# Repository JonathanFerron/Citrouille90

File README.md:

# Citrouille90
DIY keyboard project - AVR-DU based - Unibody, 90 keys plus encoder and leds - Covers PCB, FW (including BL) and case.

The PCB and case work are both licensed under a Creative Commons Attribution-NonCommercial-ShareAlike 4.0 International License (CC BY-NC-SA 4.0). The Firmware is licensed under the GNU General Public License version 3: Copyright (C) 2026 Jonathan Ferron.

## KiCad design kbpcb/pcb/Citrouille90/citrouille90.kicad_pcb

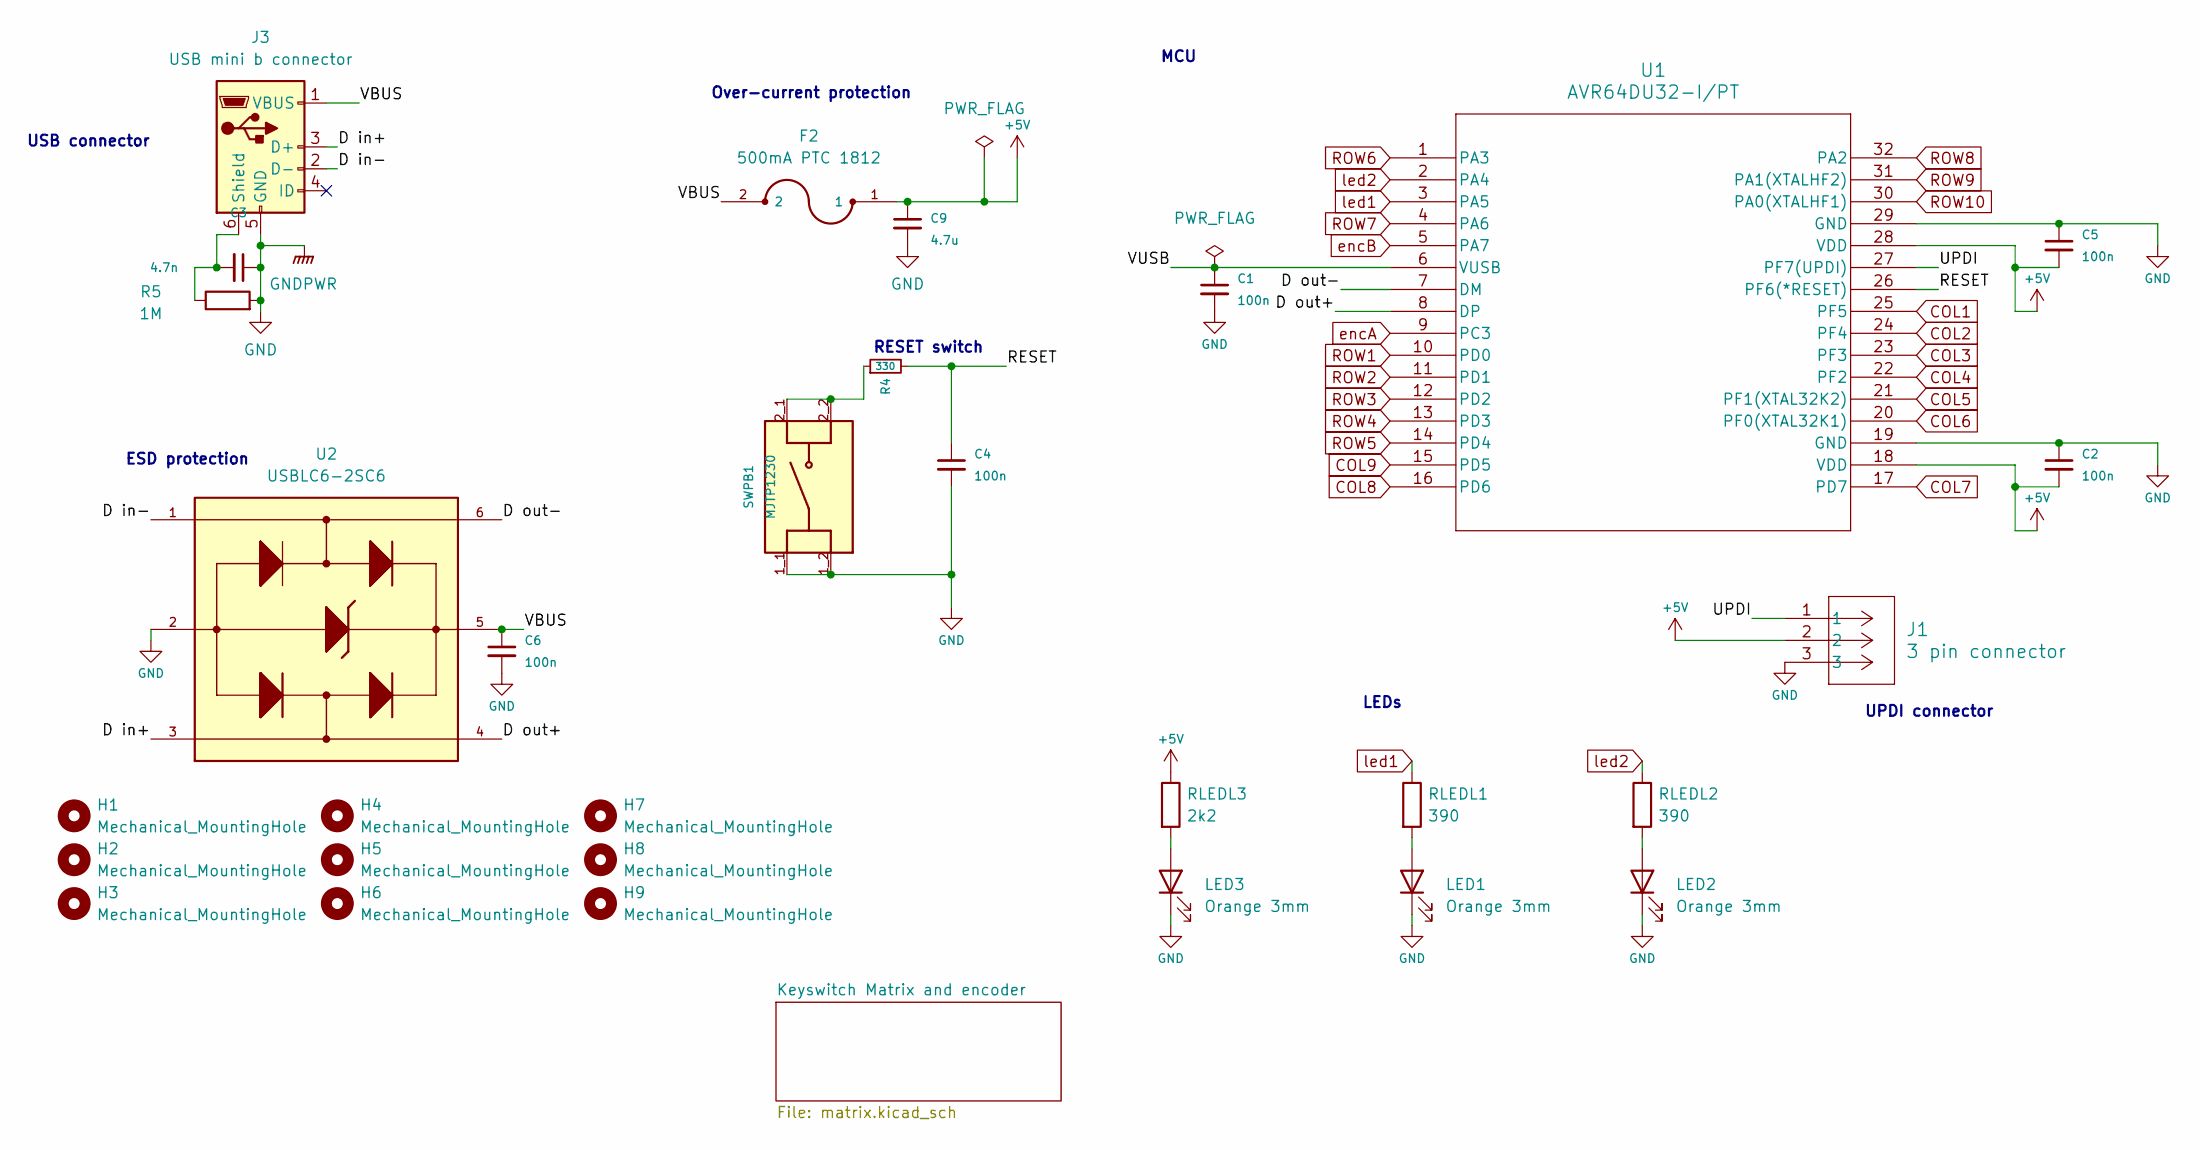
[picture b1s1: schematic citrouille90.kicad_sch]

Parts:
C1, C2, C4, C5: 100n; C_0805_2012Metric_Pad1.18x1.45mm_HandSolder; LCSC C1525
C3: 4.7n; C_0805_2012Metric_Pad1.18x1.45mm_HandSolder
C6: 100n; C_0805_2012Metric_Pad1.18x1.45mm_HandSolder
C9: 4.7u; C_1206_3216Metric_Pad1.33x1.80mm_HandSolder
F2: 500mA PTC 1812; FUSM4632X85
H1, H2, H3, H4, H5, H6, H7, H8, H9: Mechanical_MountingHole; MountingHole_2.7mm_M2.5_ISO7380_Pad
J1: 3 pin connector; PinSocket_1x03_P2.54mm_Horizontal
J3: USB mini b connector; usb mini connector
LED1, LED2, LED3: Orange 3mm; LED_D3.0mm
R4: 330; R_805
R5: 1M; R_805
RLEDL1, RLEDL2: 390; R_805
RLEDL3: 2k2; R_805
SWPB1: MJTP1230; SW_MJTP1230; PARTREV NA; LCSC C92584
U1: AVR64DU32-I/PT; TQFP32_PT_MCH-M
U2: USBLC6-2SC6; SOT-23-6

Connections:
+5V: C2.2, C5.2, C9.1, F2.1, J1.2, RLEDL3.1, U1.18 (VDD), U1.28 (VDD); also elsewhere on the board
/D out+: U1.8 (DP), U2.4; also elsewhere on the board
/D out-: U1.7 (DM), U2.6; also elsewhere on the board
/RESET: C4.1, R4.2, U1.26 (PF6(*RESET))
/UPDI: J1.1, U1.27 (PF7(UPDI))
/VBUS: C6.1, F2.2, J3.1 (VBUS), U2.5; also elsewhere on the board
/VUSB: C1.1, U1.6 (VUSB)
COL1: U1.25 (PF5); also elsewhere on the board
COL2: U1.24 (PF4); also elsewhere on the board
COL3: U1.23 (PF3); also elsewhere on the board
COL4: U1.22 (PF2); also elsewhere on the board
COL5: U1.21 (PF1(XTAL32K2)); also elsewhere on the board
COL6: U1.20 (PF0(XTAL32K1)); also elsewhere on the board
COL7: U1.17 (PD7); also elsewhere on the board
COL8: U1.16 (PD6); also elsewhere on the board
COL9: U1.15 (PD5); also elsewhere on the board
GND: C1.2, C2.1, C3.1, C4.2, C5.1, C6.2, C9.2, J1.3, J3.5 (GND), LED1.1 (K), LED2.1 (K), LED3.1 (K), R5.2, SWPB1.1_1, SWPB1.1_2, U1.19 (GND), U1.29 (GND), U2.2; also elsewhere on the board
unnamed: J3.2 (D-), U2.1
unnamed: J3.3 (D+), U2.3
unnamed 112: C3.2, J3.6 (Shield), R5.1; also elsewhere on the board
unnamed: LED1.2 (A), RLEDL1.2
unnamed: LED2.2 (A), RLEDL2.2
unnamed: LED3.2 (A), RLEDL3.2
unnamed 116: R4.1, SWPB1.2_1, SWPB1.2_2; also elsewhere on the board
ROW1: U1.10 (PD0); also elsewhere on the board
ROW2: U1.11 (PD1); also elsewhere on the board
ROW3: U1.12 (PD2); also elsewhere on the board
ROW4: U1.13 (PD3); also elsewhere on the board
ROW5: U1.14 (PD4); also elsewhere on the board
ROW6: U1.1 (PA3); also elsewhere on the board
ROW7: U1.4 (PA6); also elsewhere on the board
ROW8: U1.32 (PA2); also elsewhere on the board
ROW9: U1.31 (PA1(XTALHF2)); also elsewhere on the board
ROW10: U1.30 (PA0(XTALHF1)); also elsewhere on the board
encA: U1.9 (PC3); also elsewhere on the board
encB: U1.5 (PA7); also elsewhere on the board
led1: RLEDL1.1, U1.3 (PA5)
led2: RLEDL2.1, U1.2 (PA4)

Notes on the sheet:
Over-current protection
ESD protection
MCU
RESET switch
LEDs
UPDI connector
USB connector

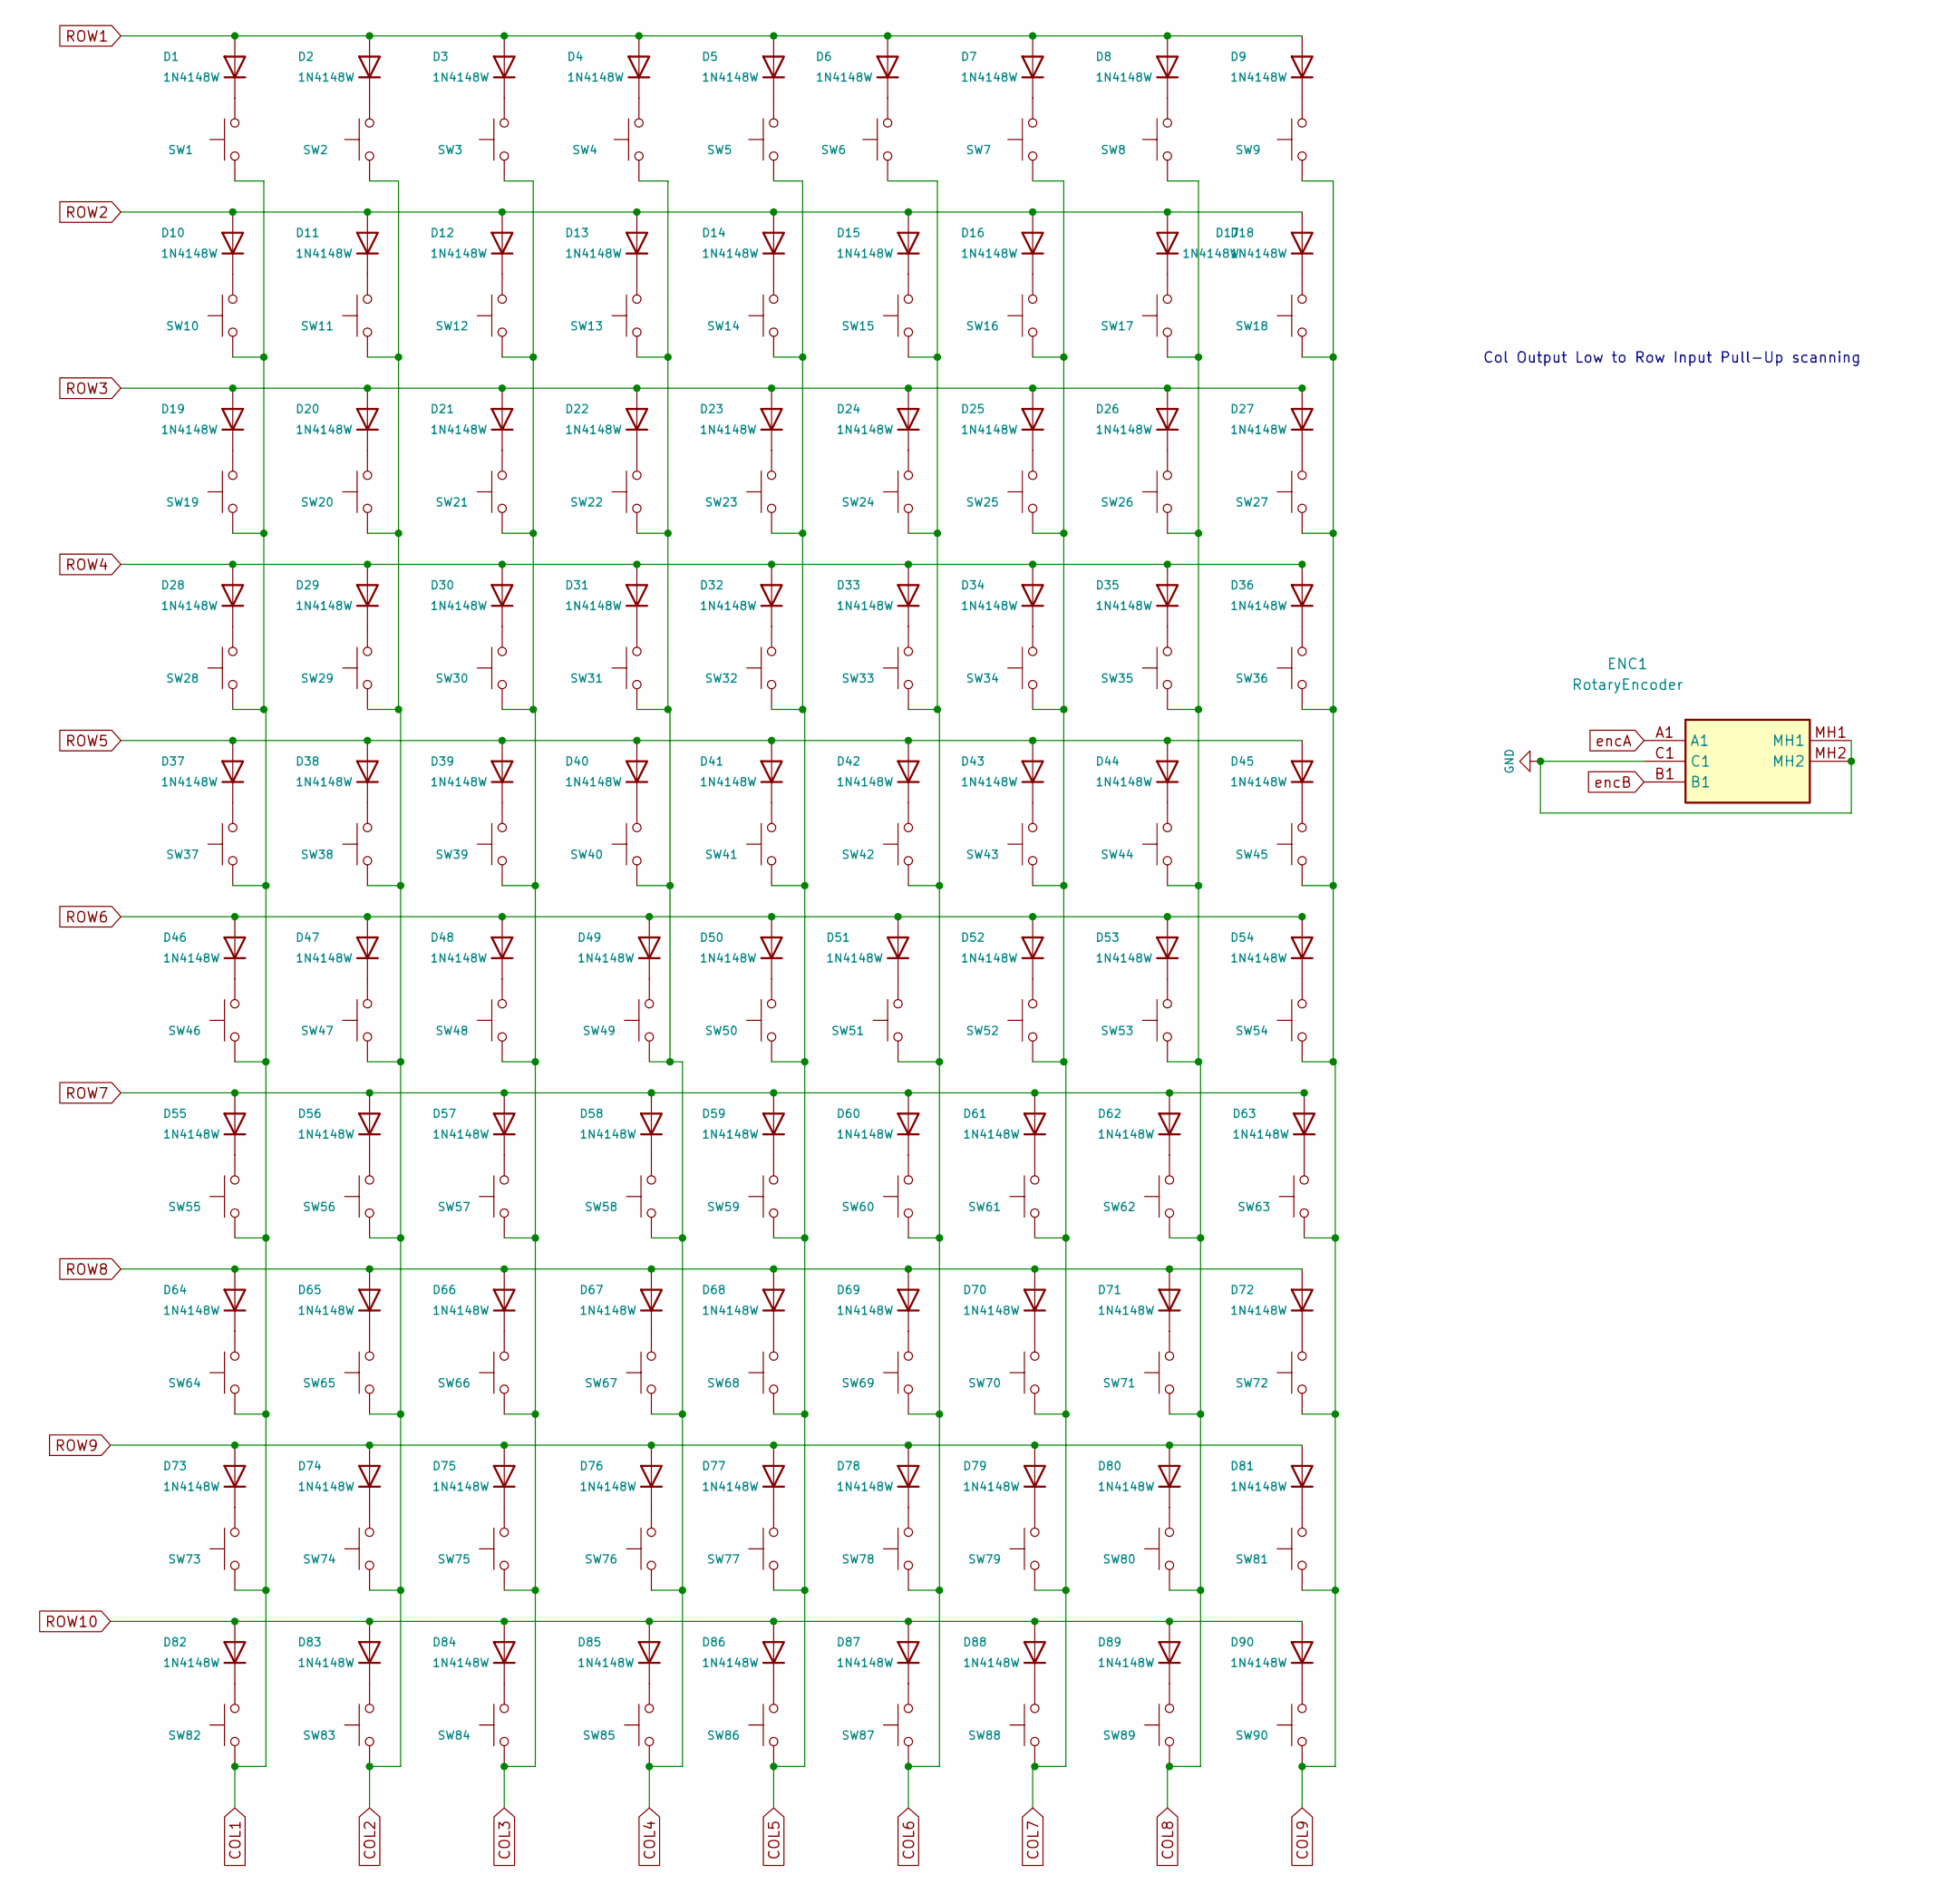
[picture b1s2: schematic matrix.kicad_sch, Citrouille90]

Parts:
D1, D2, D3, D4, D5, D6, D7, D8, D9, D10, D11, D12, D13, D14, D15, D16, D17, D18, D19, D20, D21, D22, D23, D24, D25, D26, D27, D28, D29, D30, D31, D32, D33, D34, D35, D36, D37, D38, D39, D40, D41, D42, D43, D44, D45, D46, D47, D48, D49, D50, D51, D52, D53, D54, D55, D56, D57, D58, D59, D60, D61, D62, D63, D64, D65, D66, D67, D68, D69, D70, D71, D72, D73, D74, D75, D76, D77, D78, D79, D80, D81, D82, D83, D84, D85, D86, D87, D88, D89, D90: 1N4148W; D_SOD-123; LCSC C81598
ENC1: RotaryEncoder; PES1240SN0024; Mouser Part Number 652-PES12-40S-N0024
SW1, SW2, SW3, SW4, SW5, SW6, SW7, SW8, SW9, SW10, SW11, SW12, SW13, SW14, SW15, SW16, SW17, SW18, SW19, SW20, SW21, SW22, SW23, SW24, SW25, SW26, SW27, SW28, SW29, SW30, SW31, SW32, SW33, SW34, SW35, SW36, SW37, SW38, SW39, SW40, SW41, SW42, SW43, SW44, SW45, SW46, SW47, SW48, SW49, SW50, SW51, SW52, SW53, SW54, SW55, SW56, SW57, SW58, SW59, SW60, SW61, SW62, SW63, SW64, SW65, SW66, SW67, SW68, SW69, SW70, SW71, SW72, SW73, SW74, SW75, SW76, SW77, SW78, SW79, SW80, SW81, SW82, SW83, SW84, SW85, SW86, SW87, SW88, SW89, SW90: SW_Kailh_Choc_V1_1.00u with LED indicator

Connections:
COL1: SW1.2, SW10.2, SW19.2, SW28.2, SW37.2, SW46.2, SW55.2, SW64.2, SW73.2, SW82.2; also elsewhere on the board
COL2: SW2.2, SW11.2, SW20.2, SW29.2, SW38.2, SW47.2, SW56.2, SW65.2, SW74.2, SW83.2; also elsewhere on the board
COL3: SW3.2, SW12.2, SW21.2, SW30.2, SW39.2, SW48.2, SW57.2, SW66.2, SW75.2, SW84.2; also elsewhere on the board
COL4: SW4.2, SW13.2, SW22.2, SW31.2, SW40.2, SW49.2, SW58.2, SW67.2, SW76.2, SW85.2; also elsewhere on the board
COL5: SW5.2, SW14.2, SW23.2, SW32.2, SW41.2, SW50.2, SW59.2, SW68.2, SW77.2, SW86.2; also elsewhere on the board
COL6: SW6.2, SW15.2, SW24.2, SW33.2, SW42.2, SW51.2, SW60.2, SW69.2, SW78.2, SW87.2; also elsewhere on the board
COL7: SW7.2, SW16.2, SW25.2, SW34.2, SW43.2, SW52.2, SW61.2, SW70.2, SW79.2, SW88.2; also elsewhere on the board
COL8: SW8.2, SW17.2, SW26.2, SW35.2, SW44.2, SW53.2, SW62.2, SW71.2, SW80.2, SW89.2; also elsewhere on the board
COL9: SW9.2, SW18.2, SW27.2, SW36.2, SW45.2, SW54.2, SW63.2, SW72.2, SW81.2, SW90.2; also elsewhere on the board
unnamed: D1.1 (K), SW1.1
unnamed: D2.1 (K), SW2.1
unnamed: D3.1 (K), SW3.1
unnamed: D4.1 (K), SW4.1
unnamed: D5.1 (K), SW5.1
unnamed: D6.1 (K), SW6.1
unnamed: D7.1 (K), SW7.1
unnamed: D8.1 (K), SW8.1
unnamed: D9.1 (K), SW9.1
unnamed: D10.1 (K), SW10.1
unnamed: D11.1 (K), SW11.1
unnamed: D12.1 (K), SW12.1
unnamed: D13.1 (K), SW13.1
unnamed: D14.1 (K), SW14.1
unnamed: D15.1 (K), SW15.1
unnamed: D16.1 (K), SW16.1
unnamed: D17.1 (K), SW17.1
unnamed: D18.1 (K), SW18.1
unnamed: D19.1 (K), SW19.1
unnamed: D20.1 (K), SW20.1
unnamed: D21.1 (K), SW21.1
unnamed: D22.1 (K), SW22.1
unnamed: D23.1 (K), SW23.1
unnamed: D24.1 (K), SW24.1
unnamed: D25.1 (K), SW25.1
unnamed: D26.1 (K), SW26.1
unnamed: D27.1 (K), SW27.1
unnamed: D28.1 (K), SW28.1
unnamed: D29.1 (K), SW29.1
unnamed: D30.1 (K), SW30.1
unnamed: D31.1 (K), SW31.1
unnamed: D32.1 (K), SW32.1
unnamed: D33.1 (K), SW33.1
unnamed: D34.1 (K), SW34.1
unnamed: D35.1 (K), SW35.1
unnamed: D36.1 (K), SW36.1
unnamed: D37.1 (K), SW37.1
unnamed: D38.1 (K), SW38.1
unnamed: D39.1 (K), SW39.1
unnamed: D40.1 (K), SW40.1
unnamed: D41.1 (K), SW41.1
unnamed: D42.1 (K), SW42.1
unnamed: D43.1 (K), SW43.1
unnamed: D44.1 (K), SW44.1
unnamed: D45.1 (K), SW45.1
unnamed: D46.1 (K), SW46.1
unnamed: D47.1 (K), SW47.1
unnamed: D48.1 (K), SW48.1
unnamed: D49.1 (K), SW49.1
unnamed: D50.1 (K), SW50.1
unnamed: D51.1 (K), SW51.1
unnamed: D52.1 (K), SW52.1
unnamed: D53.1 (K), SW53.1
unnamed: D54.1 (K), SW54.1
unnamed: D55.1 (K), SW55.1
unnamed: D56.1 (K), SW56.1
unnamed: D57.1 (K), SW57.1
unnamed: D58.1 (K), SW58.1
unnamed: D59.1 (K), SW59.1
unnamed: D60.1 (K), SW60.1
unnamed: D61.1 (K), SW61.1
unnamed: D62.1 (K), SW62.1
unnamed: D63.1 (K), SW63.1
unnamed: D64.1 (K), SW64.1
unnamed: D65.1 (K), SW65.1
unnamed: D66.1 (K), SW66.1
unnamed: D67.1 (K), SW67.1
unnamed: D68.1 (K), SW68.1
unnamed: D69.1 (K), SW69.1
unnamed: D70.1 (K), SW70.1
unnamed: D71.1 (K), SW71.1
unnamed: D72.1 (K), SW72.1
unnamed: D73.1 (K), SW73.1
unnamed: D74.1 (K), SW74.1
unnamed: D75.1 (K), SW75.1
unnamed: D76.1 (K), SW76.1
unnamed: D77.1 (K), SW77.1
unnamed: D78.1 (K), SW78.1
unnamed: D79.1 (K), SW79.1
unnamed: D80.1 (K), SW80.1
unnamed: D81.1 (K), SW81.1
unnamed: D82.1 (K), SW82.1
unnamed: D83.1 (K), SW83.1
unnamed: D84.1 (K), SW84.1
unnamed: D85.1 (K), SW85.1
unnamed: D86.1 (K), SW86.1
unnamed: D87.1 (K), SW87.1
unnamed: D88.1 (K), SW88.1
unnamed: D89.1 (K), SW89.1
unnamed: D90.1 (K), SW90.1
unnamed: ENC1.C1, ENC1.MH1, ENC1.MH2
ROW1: D1.2 (A), D2.2 (A), D3.2 (A), D4.2 (A), D5.2 (A), D6.2 (A), D7.2 (A), D8.2 (A), D9.2 (A); also elsewhere on the board
ROW2: D10.2 (A), D11.2 (A), D12.2 (A), D13.2 (A), D14.2 (A), D15.2 (A), D16.2 (A), D17.2 (A), D18.2 (A); also elsewhere on the board
ROW3: D19.2 (A), D20.2 (A), D21.2 (A), D22.2 (A), D23.2 (A), D24.2 (A), D25.2 (A), D26.2 (A), D27.2 (A); also elsewhere on the board
ROW4: D28.2 (A), D29.2 (A), D30.2 (A), D31.2 (A), D32.2 (A), D33.2 (A), D34.2 (A), D35.2 (A), D36.2 (A); also elsewhere on the board
ROW5: D37.2 (A), D38.2 (A), D39.2 (A), D40.2 (A), D41.2 (A), D42.2 (A), D43.2 (A), D44.2 (A), D45.2 (A); also elsewhere on the board
ROW6: D46.2 (A), D47.2 (A), D48.2 (A), D49.2 (A), D50.2 (A), D51.2 (A), D52.2 (A), D53.2 (A), D54.2 (A); also elsewhere on the board
ROW7: D55.2 (A), D56.2 (A), D57.2 (A), D58.2 (A), D59.2 (A), D60.2 (A), D61.2 (A), D62.2 (A), D63.2 (A); also elsewhere on the board
ROW8: D64.2 (A), D65.2 (A), D66.2 (A), D67.2 (A), D68.2 (A), D69.2 (A), D70.2 (A), D71.2 (A), D72.2 (A); also elsewhere on the board
ROW9: D73.2 (A), D74.2 (A), D75.2 (A), D76.2 (A), D77.2 (A), D78.2 (A), D79.2 (A), D80.2 (A), D81.2 (A); also elsewhere on the board
ROW10: D82.2 (A), D83.2 (A), D84.2 (A), D85.2 (A), D86.2 (A), D87.2 (A), D88.2 (A), D89.2 (A), D90.2 (A); also elsewhere on the board

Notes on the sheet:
Col Output Low to Row Input Pull-Up scanning

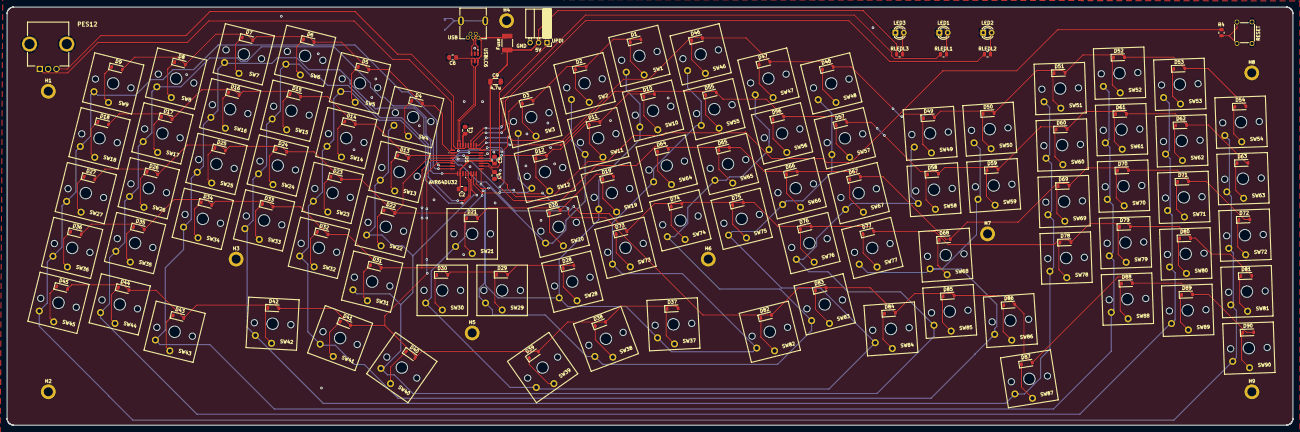
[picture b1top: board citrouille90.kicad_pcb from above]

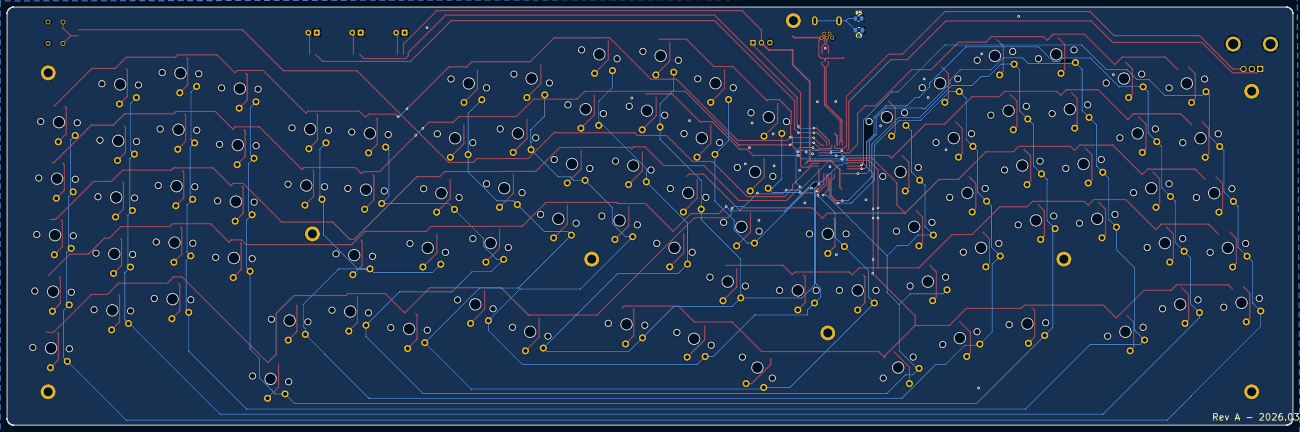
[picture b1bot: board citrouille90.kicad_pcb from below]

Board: 2 copper layers, 386.7 x 125.7 mm, 211 parts (2 on the bottom side), 128 nets.

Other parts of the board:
Fuse: 500mA PTC 1812; FUSM4632X85
PES12: RotaryEncoder; PES1240SN0024
RESET: MJTP1230; SW_MJTP1230
USB: USB mini b connector; usb mini connector
USBLC6: USBLC6-2SC6; SOT-23-6

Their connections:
+5V: Fuse.1; also elsewhere on the board
/D in+: USB.3 (D+), USBLC6.3
/D in-: USB.2 (D-), USBLC6.1
/D out+: USBLC6.4; also elsewhere on the board
/D out-: USBLC6.6; also elsewhere on the board
/VBUS: Fuse.2, USB.1 (VBUS), USBLC6.5; also elsewhere on the board
GND: PES12.C1, PES12.MH1, PES12.MH2, RESET.1_1, RESET.1_2, USB.5 (GND), USBLC6.2; also elsewhere on the board
unnamed 112: USB.6; also elsewhere on the board
unnamed 116: RESET.2_1, RESET.2_2; also elsewhere on the board
encA: PES12.A1; also elsewhere on the board
encB: PES12.B1; also elsewhere on the board

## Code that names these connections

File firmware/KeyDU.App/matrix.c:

/* matrix.c — Key matrix scan for Citrouille90 / AVR64DU32
 * Column-output-low / row-input-pullup scheme.
 * SPDX-License-Identifier: GPL-3.0-or-later
 *
 * Pin assignment (32-pin package):
 *
 *   Columns (output)
 *     PF0–PF5  →  cols 1–6   (COL_F_MASK 0x3F)
 *     PD5–PD7  →  cols 7–9   (COL_D_MASK 0xE0)
 *
 *   Rows (input, pull-up, active-low)
 *     PD0–PD4  →  rows 1–5   (ROW_D_MASK 0x1F)
 *     PA3      →  row  6
 *     PA6      →  row  7
 *     PA2      →  row  8
 *     PA1      →  row  9
 *     PA0      →  row 10     (ROW_A_MASK 0x4F)
 *
 * Note: PORTD is mixed — PD0–PD4 are row inputs, PD5–PD7 are col outputs.
 */

#include <avr/io.h>
#include <stdint.h>
#include "gpio.h"
#include "matrix.h"

/* ---------------------------------------------------------
 * Port-wide masks
 * --------------------------------------------------------- */
#define COL_F_MASK  0x3F    /* PF0–PF5  cols 1–6  */
#define COL_D_MASK  0xE0    /* PD5–PD7  cols 7–9  */
#define ROW_D_MASK  0x1F    /* PD0–PD4  rows 1–5  */
#define ROW_A_MASK  0x4F    /* PA0–PA3, PA6 rows 6–10 */

/* ---------------------------------------------------------
 * Column pin descriptors
 * --------------------------------------------------------- */
static const gpio_pin_t COL_1  = GPIO_PIN(PORTF, 0);
static const gpio_pin_t COL_2  = GPIO_PIN(PORTF, 1);
static const gpio_pin_t COL_3  = GPIO_PIN(PORTF, 2);
static const gpio_pin_t COL_4  = GPIO_PIN(PORTF, 3);
static const gpio_pin_t COL_5  = GPIO_PIN(PORTF, 4);
static const gpio_pin_t COL_6  = GPIO_PIN(PORTF, 5);
static const gpio_pin_t COL_7  = GPIO_PIN(PORTD, 5);
static const gpio_pin_t COL_8  = GPIO_PIN(PORTD, 6);
static const gpio_pin_t COL_9  = GPIO_PIN(PORTD, 7);

/* ---------------------------------------------------------
 * Row pin descriptors (init only — pull-up config)
 * --------------------------------------------------------- */
static const gpio_pin_t ROW_1  = GPIO_PIN(PORTD, 0);
static const gpio_pin_t ROW_2  = GPIO_PIN(PORTD, 1);
static const gpio_pin_t ROW_3  = GPIO_PIN(PORTD, 2);
static const gpio_pin_t ROW_4  = GPIO_PIN(PORTD, 3);
static const gpio_pin_t ROW_5  = GPIO_PIN(PORTD, 4);
static const gpio_pin_t ROW_6  = GPIO_PIN(PORTA, 3);
static const gpio_pin_t ROW_7  = GPIO_PIN(PORTA, 6);
static const gpio_pin_t ROW_8  = GPIO_PIN(PORTA, 2);
static const gpio_pin_t ROW_9  = GPIO_PIN(PORTA, 1);
static const gpio_pin_t ROW_10 = GPIO_PIN(PORTA, 0);

/* ---------------------------------------------------------
 * PORTA row bit -> logical row index (0-based)
 * __builtin_ctz(bit) gives the pin number as the LUT index.
 *   PA0 → row 9   PA1 → row 8   PA2 → row 7
 *   PA3 → row 5   PA6 → row 6
 * 0xFF marks unused/invalid entries.
 * --------------------------------------------------------- */
static const uint8_t row_a_lut[8] = {
    9, 8, 7, 5, 0xFF, 0xFF, 6, 0xFF
};

/* ---------------------------------------------------------
 * matrix_init
 * --------------------------------------------------------- */
void matrix_init(void) {
    /* Columns: latch high before enabling output to avoid glitch */
    PORTF.OUTSET = COL_F_MASK;
    PORTF.DIRSET = COL_F_MASK;
    PORTD.OUTSET = COL_D_MASK;
    PORTD.DIRSET = COL_D_MASK;

    /* Rows: inputs at reset by default — enable pull-ups only */
    GPIO_PULLUP_ENABLE(ROW_1);
    GPIO_PULLUP_ENABLE(ROW_2);
    GPIO_PULLUP_ENABLE(ROW_3);
    GPIO_PULLUP_ENABLE(ROW_4);
    GPIO_PULLUP_ENABLE(ROW_5);
    GPIO_PULLUP_ENABLE(ROW_6);
    GPIO_PULLUP_ENABLE(ROW_7);
    GPIO_PULLUP_ENABLE(ROW_8);
    GPIO_PULLUP_ENABLE(ROW_9);
    GPIO_PULLUP_ENABLE(ROW_10);
}

/* ---------------------------------------------------------
 * scan_col — drive one column low, read both row ports,
 *            dispatch any active (low) rows, release column.
 * --------------------------------------------------------- */
static inline void scan_col(const gpio_pin_t col, uint8_t col_idx) {
    GPIO_LOW(col);
    __builtin_avr_nop();                        /* RC settle */

    uint8_t rows_d = ~PORTD.IN & ROW_D_MASK;   /* single IN read */
    uint8_t rows_a = ~PORTA.IN & ROW_A_MASK;   /* single IN read */

    GPIO_HIGH(col);

    /* PORTD rows: PD0–PD4 map directly to row indices 0–4 */
    uint8_t rd = rows_d;
    while (rd) {
        uint8_t bit = rd & -rd;                 /* isolate lowest set bit */
        register_key(col_idx, __builtin_ctz(bit));
        rd &= rd - 1;                           /* clear lowest set bit   */
    }

    /* PORTA rows: non-contiguous pins resolved via LUT */
    uint8_t ra = rows_a;
    while (ra) {
        uint8_t bit = ra & -ra;
        register_key(col_idx, row_a_lut[__builtin_ctz(bit)]);
        ra &= ra - 1;
    }
}

/* ---------------------------------------------------------
 * matrix_scan — call once per 1KHz tick
 * --------------------------------------------------------- */
void matrix_scan(void) {
    scan_col(COL_1, 0);
    scan_col(COL_2, 1);
    scan_col(COL_3, 2);
    scan_col(COL_4, 3);
    scan_col(COL_5, 4);
    scan_col(COL_6, 5);
    scan_col(COL_7, 6);
    scan_col(COL_8, 7);
    scan_col(COL_9, 8);
}

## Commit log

2026-03-11 Majority of PCB design
2026-03-14 Expand licensing and disclaimer sections in README
    Added detailed licensing information for hardware, firmware, and artwork, along with a disclaimer.
2026-03-14 Add LICENSE-FIRMWARE file
2026-03-19 Update documentation and plans
2026-03-19 Early firmware coding research
2026-03-19 PCB work
2026-03-19 Fine tune PCB
2026-03-25 Fine tune silkscreen graphics
2026-03-28 Firmware code research and decisions
2026-03-31 Add RC filter to encoder
2026-04-07 start generating firmware code
2026-05-01 Clean split of HW and FW in two separate repos
2026-05-16 Final update to PCB prior to generation of gerber and drill files
2026-05-17 Update documentation, generate gerbers
